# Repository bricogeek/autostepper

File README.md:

AutoStepper
=========
Oscar Gonzalez July 2016

AVR ATmega32U4 based board to control a stepper motor

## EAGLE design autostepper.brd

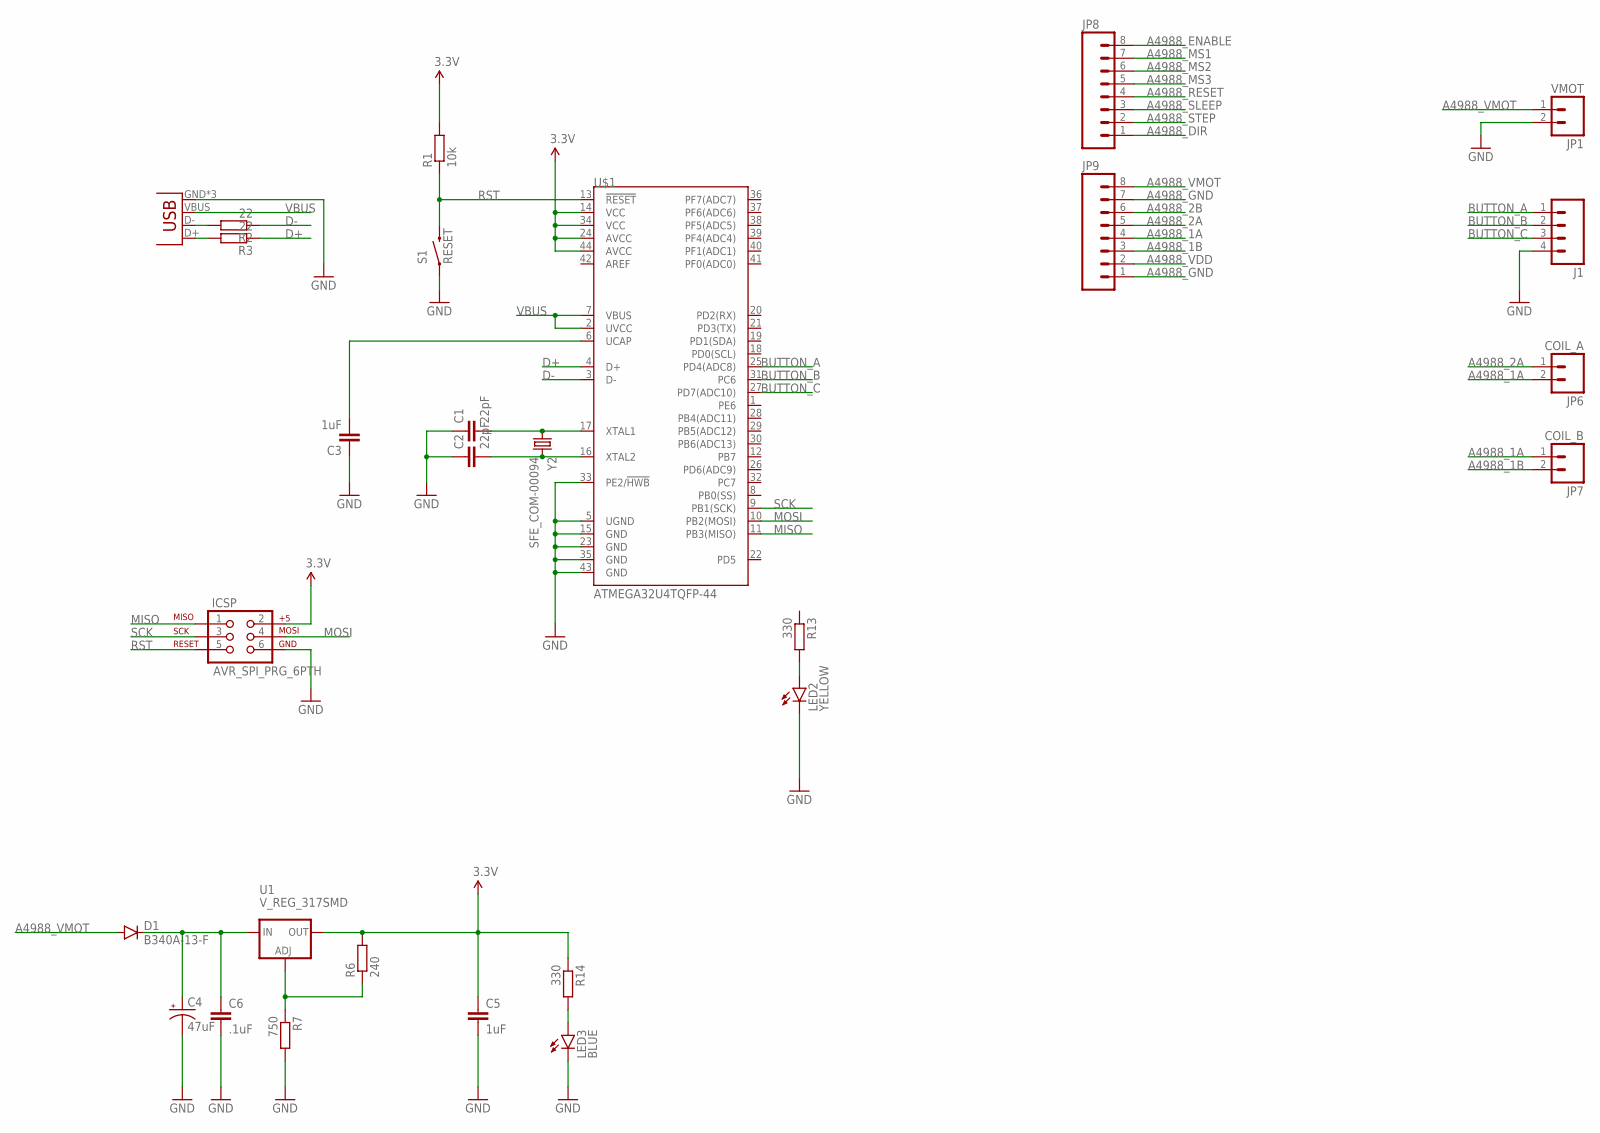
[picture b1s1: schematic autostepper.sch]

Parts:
C1, C2: 22pF; 1206
C3, C5: 1uF; 1206
C4: 47uF; PANASONIC_D
C6: .1uF; 1206
D1: B340A-13-F; DIODE-HV
ICSP: AVR_SPI_PRG_6PTH; 2X3
J1: M04LONGPADS; 1X04_LONGPADS
JP1: VMOT; SCREWTERMINAL-5MM-2
JP2: USB-MICROB
JP6: COIL_A; SCREWTERMINAL-5MM-2
JP7: COIL_B; SCREWTERMINAL-5MM-2
JP8, JP9: M08LONGPADS; 1X08_LONGPADS
LED2: YELLOW; LED-0603
LED3: BLUE; LED-0603
R1: 10k; M0805
R2, R3: 22; M0805
R6: 240; M0805
R7: 750; M0805
R13, R14: 330; M0805
S1: RESET; TACTILE-SWITCH-SMD
U1: V_REG_317SMD; SOT223
U$1: ATMEGA32U4TQFP-44; TQFP44
Y2: SFE_COM-00094; CRYSTAL-SMD-5X3

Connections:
3.3V: C5.1, ICSP.2, R1.2, R6.2, R14.1, U1.2 (OUT), U$1.14 (VCC), U$1.24 (AVCC), U$1.34 (VCC), U$1.44 (AVCC)
A4988_1A: JP6.2, JP7.1, JP9.4
A4988_1B: JP7.2, JP9.3
A4988_2A: JP6.1, JP9.5
A4988_2B: JP9.6
A4988_DIR: JP8.1
A4988_ENABLE: JP8.8
A4988_GND: JP9.1, JP9.7
A4988_MS1: JP8.7
A4988_MS2: JP8.6
A4988_MS3: JP8.5
A4988_RESET: JP8.4
A4988_SLEEP: JP8.3
A4988_STEP: JP8.2
A4988_VDD: JP9.2
A4988_VMOT: D1.A, JP1.1, JP9.8
BUTTON_A: J1.1, U$1.25 (PD4(ADC8))
BUTTON_B: J1.2, U$1.31 (PC6)
BUTTON_C: J1.3, U$1.27 (PD7(ADC10))
D+: R3.1, U$1.4 (D+)
D-: R2.1, U$1.3 (D-)
GND: C1.1, C2.1, C3.1, C4.-, C5.2, C6.2, ICSP.6, J1.4, JP1.2, JP2.GND, JP2.MT1 (GND), JP2.MT2 (GND), LED2.C, LED3.C, R7.2, S1.1, U$1.5 (UGND), U$1.15 (GND), U$1.23 (GND), U$1.33 (PE2/!HWB), U$1.35 (GND), U$1.43 (GND)
MISO: ICSP.1, U$1.11 (PB3(MISO))
MOSI: ICSP.4, U$1.10 (PB2(MOSI))
unnamed: C1.2, U$1.17 (XTAL1), Y2.1
unnamed: C2.2, U$1.16 (XTAL2), Y2.3 (2)
unnamed: JP2.D-, R2.2
unnamed: JP2.D+, R3.2
unnamed: C3.2, U$1.6 (UCAP)
unnamed: R6.1, R7.1, U1.1 (ADJ)
unnamed: C4.+, C6.1, D1.C, U1.3 (IN)
unnamed: LED2.A, R13.2
unnamed: LED3.A, R14.2
RST: ICSP.5, R1.1, S1.3 (2), U$1.13 (!RESET)
SCK: ICSP.3, U$1.9 (PB1(SCK))
VBUS: JP2.VBUS, U$1.2 (UVCC), U$1.7 (VBUS)

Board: 2 copper layers, 32 parts (10 on the bottom side), 26 nets, no tracks yet.

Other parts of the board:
U$2, U$4, U$5, U$6: STAND-OFF

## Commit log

2016-07-29 Connectors added
2016-08-01 Layout fix

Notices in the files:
parts and their libraries:
SparkFun-Electromechanical: Licensing: Creative Commons ShareAlike 4.0 International - https://creativecommons.org/licenses/by-sa/4.0
